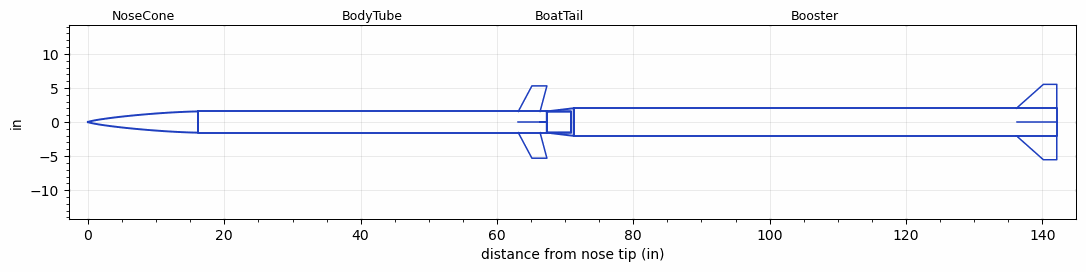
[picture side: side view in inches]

<RASAeroDocument>
 <FileVersion>2</FileVersion>
 <RocketDesign>
  <NoseCone>
   <Length>16.142</Length>
   <Diameter>3.11</Diameter>
   <Shape>Von Karman Ogive</Shape>
   <Location>0</Location>
  </NoseCone>
  <BodyTube>
   <Length>51.182</Length>
   <Diameter>3.11</Diameter>
   <Location>16.142</Location>
   <BoattailLength>3.543</BoattailLength>
   <BoattailRearDiameter>3.1</BoattailRearDiameter>
   <Fin>
    <Count>4</Count>
    <Chord>3.2</Chord>
    <Span>3.75</Span>
    <SweepDistance>2</SweepDistance>
    <TipChord>2.2</TipChord>
    <Thickness>0.1969</Thickness>
    <LERadius>0.01</LERadius>
    <Location>4.2</Location>
    <AirfoilSection>Hexagonal</AirfoilSection>
    <FX1>1</FX1>
    <FX3>1</FX3>
   </Fin>
  </BodyTube>
  <BoatTail>
   <Length>3.543</Length>
   <Diameter>3.11</Diameter>
   <RearDiameter>3.1</RearDiameter>
   <Location>67.324</Location>
  </BoatTail>
  <Booster>
   <Length>70.866</Length>
   <Diameter>4.055</Diameter>
   <InsideDiameter>3.11</InsideDiameter>
   <Location>67.324</Location>
   <ShoulderLength>3.937</ShoulderLength>
   <Fin>
    <Count>4</Count>
    <Chord>5.906</Chord>
    <Span>3.5</Span>
    <SweepDistance>3.94</SweepDistance>
    <TipChord>1.969</TipChord>
    <Thickness>0.1969</Thickness>
    <LERadius>0.01</LERadius>
    <Location>5.906</Location>
    <AirfoilSection>Hexagonal</AirfoilSection>
    <FX1>1</FX1>
    <FX3>1</FX3>
   </Fin>
  </Booster>
  <Surface>Smooth Paint</Surface>
  <ModifiedBarrowman>False</ModifiedBarrowman>
  <Turbulence>True</Turbulence>
  <UseBooster1>False</UseBooster1>
  <UseBooster2>False</UseBooster2>
 </RocketDesign>
 <LaunchSite>
  <Altitude>0</Altitude>
  <Pressure>0</Pressure>
  <RodAngle>0</RodAngle>
  <RodLength>16</RodLength>
  <Temperature>74</Temperature>
  <WindSpeed>0</WindSpeed>
 </LaunchSite>
 <Recovery>
  <Altitude1>1000</Altitude1>
  <Altitude2>1700</Altitude2>
  <DeviceType1>Parachute</DeviceType1>
  <DeviceType2>Parachute</DeviceType2>
  <Event1>False</Event1>
  <Event2>False</Event2>
  <Size1>1</Size1>
  <Size2>1</Size2>
  <EventType1>Apogee</EventType1>
  <EventType2>Altitude</EventType2>
  <CD1>1.33</CD1>
  <CD2>1.33</CD2>
 </Recovery>
 <SimulationList>
  <Simulation>
   <SustainerEngine>M2045-BS  (CTI)</SustainerEngine>
   <SustainerLaunchWt>19.3</SustainerLaunchWt>
   <SustainerNozzleDiameter>1.23</SustainerNozzleDiameter>
   <SustainerCG>44.8</SustainerCG>
   <SustainerIgnitionDelay>15</SustainerIgnitionDelay>
   <Booster1Engine>O3400-IM-P  (CTI)</Booster1Engine>
   <Booster1LaunchWt>66.8</Booster1LaunchWt>
   <Booster1SeparationDelay>0</Booster1SeparationDelay>
   <Booster1IgnitionDelay>0</Booster1IgnitionDelay>
   <Booster1CG>90.53</Booster1CG>
   <Booster1NozzleDiameter>1.75</Booster1NozzleDiameter>
   <IncludeBooster1>True</IncludeBooster1>
   <Booster2Delay>0</Booster2Delay>
   <IncludeBooster2>False</IncludeBooster2>
   <TimetoApogee>104.4326</TimetoApogee>
   <MaxAltitude>145543.7</MaxAltitude>
   <MaxVelocity>3845.496</MaxVelocity>
  </Simulation>
 </SimulationList>
</RASAeroDocument>
